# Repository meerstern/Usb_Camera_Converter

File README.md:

#  USBカメラ変換基板
#  Usb_Camera_Converter 
This board with PIC32MZ is a converter that captures from a UVC(Usb Video Class) standard Usb camera and converts it to a BMP or JPG image.

  * 10秒間隔インターバル記録した映像をコマ送り編集で動画化した例  
 
## 概要
  * 本変換基板はUVC規格のUsbカメラからキャプチャしてBMPもしくはJPG画像に変換する基板です  
  * シリアルUARTコマンドもしくは基板上のボタンを押すことで画像ファイルとして記録されます  
  * インターバル設定をすることで設定した秒数間隔(1秒~最長6か月程度)で自動的にインターバル記録できます  
  * 変換した画像はTFカード(microSD互換)もしくはXmodem、Ymodemでマイコン等に転送できます  
  * 時刻管理(RTC)を内蔵しており、自動的に日付のフォルダを生成し、日付日時のファイル名で保存されます  
  * 保存可能なファイル形式(BMP/JPG)および解像度は接続するUsbカメラによって異なります
  * PCを介したシリアルコンソール上でインターバル設定やファイル形式、解像度等の設定が可能です  
  * 高フレームレートを要求しない、簡易的な記録や監視に適しています  
  
## 仕様
  * 電源電圧5V、電流800mA(microUSBもしくはピンヘッダから供給)以上の電源  
  * 時刻管理用電池CR1220搭載  
  * PIC32MZ USB HighSpeed(480MHz) Host機能によるUVCホスト(USBタイプA)  
  * PCを介したシリアルコンソール上から変更できるパラメータ:  
  記録インターバル、ファイル形式、画像解像度、日付時刻、  
  代替インタフェース設定、データフレームインターバル  
  * microTFカード対応(microSD、microSDHC、microSDXC互換)、128GBまで動作確認済  
  * 3色状態表示LED(青:電源、緑:ストリーミング中、赤:ストリーミングエラー)  
  * シリアルコンソールボーレート9600bps、データサイズ8bit、パリティ無、ストップ1bitが既定値です  
  * シリアルコンソール用のUsbドライバ(PL2303GL)は[Windows版][2]、[Mac版][3]して使用してください  
  * Linux版のシリアルコンソール用のUsbドライバはKernel 2.4.31以降、標準で組み込まれています  
  * microTFカードを介したファームウェアアップデート対応  
  * 各設定パラメータ情報は時刻と一緒に保持されます  
  * 基板サイズ25mm x65mm、穴M3x4(間隔19mm x43mm)  

## シリアルコンソール
  * インタラクティブなシリアルコンソールから各種設定を変更することができます  
  * ボーレート9600bps、データサイズ8bit、パリティ無、ストップ1bitが既定値です  
  * 日時コマンド一覧は下記の通りです  
  
| コマンド名 | コマンド | 引数 | 例 | 
|:-----------|:------------|:------------|:------------|
| 時刻設定 | tim= | hhmmss | tim=220212(Enterキー) |
| 時刻確認 | tim? | なし | tim?(Enterキー) |
| 日時設定 |	day= | YYMMDD | day=220305(Enterキー) | 
| 日時確認 |	day? | なし | day?(Enterキー) | 	

  * カメラ機能コマンド一覧は下記の通りです  

| コマンド名 | コマンド | 引数 | 例 | 
|:-----------|:------------|:------------|:------------|
| 条件取得 | dsps | なし | dsps(Enterキー) |
| 条件設定 | idx= | インデックス番号 | idx=12(Enterキー) |
|　条件確認 | idx? | なし | idx?(Enterキー) | 
|　画像取得(TFカード) | trg! | なし | trg!(Enterキー) | 
|　画像取得(xmodem) | xmd! | なし | xmd!(Enterキー) | 
|　画像取得(ymodem) | ymd! | なし | ymd!(Enterキー) | 
| インターバル設定 | int= | 秒数 | int=5(Enterキー) | 	
| インターバル確認 | int? | なし | int?(Enterキー) | 	
| 代替インタフェース設定 | alt= | インデックス番号 | alt=2(Enterキー) | 	
| 代替インタフェース確認 | alt? | なし | alt?(Enterキー) | 	
| データフレームインターバル設定 | dfi= | インデックス番号 | dfi=2(Enterキー) | 	
| データフレームインターバル確認 | dfi? | なし | dfi?(Enterキー) | 
| Bmp形式白黒変換モード設定 | mon= | 0 or 1 | mon=1(Enterキー) | 	
| Bmp形式白黒変換モード確認 | mon? | なし | mon?(Enterキー) | 

  * インターバル記録しない場合はint=-1を設定します  
  * 代替インタフェース設定を自動にする場合はalt=0を設定します(既定値)  
  * 代替インタフェースは1回のデータ転送のサイズを決定します  
  * 1回のデータ転送サイズが小さすぎる場合は画像フレームのタイミングに間に合わない可能性があります  
  * 1回のデータ転送サイズが大きすぎる場合は処理しきれない場合があります  
  * カメラの機種によって設定可能な代替インタフェース数やサイズが異なります  
  * Bmp形式白黒変換モードはファームバージョンv1.1.0以降で対応しています  
  * Bmp形式白黒変換モードはデフォルトでは無効化されています  
  * Bmp形式白黒変換モードは電源再投入やリセット等で設定が無効化されます  
  
  <br>

  * データフレームインターバルを自動にする場合はdfi=0を設定します(既定値)  
  * データフレームインターバルはデータ転送の間隔、カメラのフレームレートを決定します  
  * データフレームインターバルが短かすぎる場合、処理が間に合わない可能性があります  
  * データフレームインターバルが長すぎる場合、トリガを掛けてから保存されるまで時間を要する場合があります  
  * カメラの機種によって対応するデータフレームインターバルの数や大きさが異なります  
  
  * システム機能のコマンド一覧は下記の通りです  
  
| コマンド名 | コマンド | 引数 | 例 | 
|:-----------|:------------|:------------|:------------|
| ボーレート設定 | brt= | ボーレート | brt=9600(Enterキー) |
| ボーレート確認 | brt? | なし | brt?(Enterキー) |
| ソフトリセット |	rst! | なし | rst!(Enterキー) | 
| 一時停止 |	pus! | なし | pus?(Enterキー) | 	  
| 再開 |	rsm! | なし | rsm?(Enterキー) |
| ファームアップデート |	fup! | なし | fup?(Enterキー) |
| ヘルプ確認 |	help | なし | help(Enterキー) |

## 使い方  
### a.単体で使用する場合  
  1. 本変換基板のmicroUSBをPC等に接続し、Teraterm等からシリアルコンソールにアクセスします    
  2. Usbカメラを変換基板のUsbコネクタに接続します
  3. 初期設定状態で動作開始します(初期設定ではエラーメッセージが出る場合があります)
  4. dspsコマンドで設定可能な条件を表示します  
  5. 設定したいファイル形式、解像度の条件をインデックス番号でidxコマンドを用いて設定します  
  6. rst!コマンドでソフトリセットさせて設定した内容を反映させます  
  7. microTFカードを挿入します
  8. ストリーミング中を示す緑ランプが点灯したことを確認します 点灯しない場合は5.で別の番号を設定します  
  9. trg!コマンドもしくはボタンを押すと画像が保存されます    
  
### b.連携して使用する場合    
  1. 事前にPC等からa.の設定したいファイル形式、解像度の条件を設定します
  2. 本変換基板の外部電源に5Vを供給し、TX、RXをマイコン等に接続します    
  3. Usbカメラを変換基板のUsbコネクタに接続します
  4. microTFカードを挿入します
  5. ストリーミング中を示す緑ランプが点灯したことを確認します  
  6. trg!コマンドもしくはtrgピンをGNDに接続することで画像が保存されます  
  7. xmd!コマンドを送信後、xmodem(チェックサム有効)で受信できます  
  8. ymd!コマンドを送信後、ymodemで受信できます   
  9. ユーザ側でコードを実装することでSPI等を介して外部機器と通信できます  
  
### c.日付/時刻設定する場合
  1. 本変換基板のmicroUSBをPC等に接続し、Teraterm等からシリアルコンソールにアクセスします   
  2. day=コマンドで日付を設定します 例 22年3月14日の場合はday=220314(Enter)と入力します  
  3. tim=コマンドで時刻を設定します 例 午後1時23分34秒の場合はtim=132334(Enter)と入力します  
  4. day?コマンド、tim?コマンドで設定された日付、日時を確認します  　
  
   * 日付、時刻が1桁の場合は0で桁を埋めてください 

### d.ファームウェアアップデートする場合
  1. アップデートしたいファームウェアをTFカードのディレクトリ直下にいれます  
  2. ファイル名をimage.binに変更します  
  3. 変換基板にTFカードを挿入し、電源を供給します  
  4. Teraterm等からシリアルコンソールからfup!コマンドを実行します  
  5. 自動的に再起動し、ファームウェアアップデートが開始されます  
  6. Update Successを確認するかシリアルコンソールに表示されるバージョンを確認してください  

## 注意点
  * マイコン上で処理する都合上、完全なUVC規格でありません  
  * カメラによって動作しないor不安定な場合があります  
  * 動作確認済のUsbカメラはTestedCamera.csvをご確認ください  
  * ハイビジョン対応等の高機能カメラよりも200万画素程度の単機能カメラの方が安定して動く傾向があります  
  * 動画を切り出して画像に変換するため、最高でも1FPSです 高フレームレートを要求する用途には適しません  
  * ボタンやコマンドから取得命令後、ストリーミングデータから切り出し処理の都合上、タイムラグがあります  
  * BMP形式の場合、メモリの制約によって最大解像度は320x240です  
  * JPG形式の場合、解像度によって動作、非動作の場合があります  
  * 動画ファイル形式の記録はできません  
  * 電源不安定や電流が足りない場合、動作確認済のカメラであっても正常に動作しない場合があります  
  * 電流が足りない場合、microUSBとJ5 5Vピンの両方から5V電源を供給することで動作する場合があります  
  * フォーマット、解像度のインデックス番号はカメラ機種によって番号や設定可能な条件数が異なります  
  * カメラによってはBMPをサポートしていないカメラがあります  
  * モードによって動作しない場合、下記の設定を変更することで動作する場合があります  
   -代替インタフェース設定(altコマンド)  
   -データフレームインターバル設定(dfiコマンド) 
  * 設定を変更することで必ず動作できる保証はありません   
  * Xmodem/Ymodemによる転送は9600bpsの場合、1枚の画像で数10分前後転送に要します  
  * 各設定はソフトリセット後もしくは電源再投入後に反映されます  
  * 時刻管理電池の消耗や交換した場合、各設定パラメータ、時刻はリセットされます  
  * ファームウェアアップデート時はボーレート9600bpsで固定です   

## ファームウェアビルド方法
  * MPLAB X v5.45/XC32 v2.50/Harmoney3以降を用いてビルドしてください  
  * ブートローダ用のAppファームをビルドする際はリンカファイルにp32MZ2048EFG100withBOOTLD.ldを選択します  
  * 生成されたAppファームの*.binファイルをimage.binに変更してSDカードから更新コマンドを用いて更新してください    
  * デバッグ等でブートローダ未使用でファームをビルドする際はリンカファイルにp32MZ2048EFG100.ldを選択します  
  * 再度、ブートローダを書き込む際にはUsbCamBoot_v.XX_XXXXXX.hexをIPE等から書き込んでください  
  
## 応用編
  * LCDファームに書き換えることでSPI対応LCD(160x128、ST7735S)でモニタすることが可能です  
  * LCDモニタはBMPの場合、160x120解像度のみ対応しています    
  * ENABLE_JPGDECODEを有効化することでTJPGD3ライブラリを用いてJPGからBMPにデコードして描画できます    
  　解像度幅160、320、640、1280のみ、一部のカメラは未対応  
  * コードを公開しています 改造することで他の機器とすることが可能です  
  * UART(XMODEM/YMODEM)に比べてSPIを介して高速に転送できます  

| LCDピン | 変換基板ピン |  
|:-----------|:------------|
| VCC,LED | J7 3.3V | 
| GND | J7 GND | 
| CS |	J7 CS | 
| SCK |	J7 SCK |   
| SDA |	J7 MOSI | 
| AO |	J3 PGED | 
| RST |	J3 PGEC | 

## 販売サイト
  * [スイッチサイエンス][4]

[2]: https://www.prolific.com.tw/UserFiles/files/PL23XX_Prolific_DriverInstaller_v408.zip
[3]: https://www.prolific.com.tw/UserFiles/files/PL2303HXD_G_Mac%20Driver_v2_1_0_20210311.zip
[4]: https://www.switch-science.com/products/8130

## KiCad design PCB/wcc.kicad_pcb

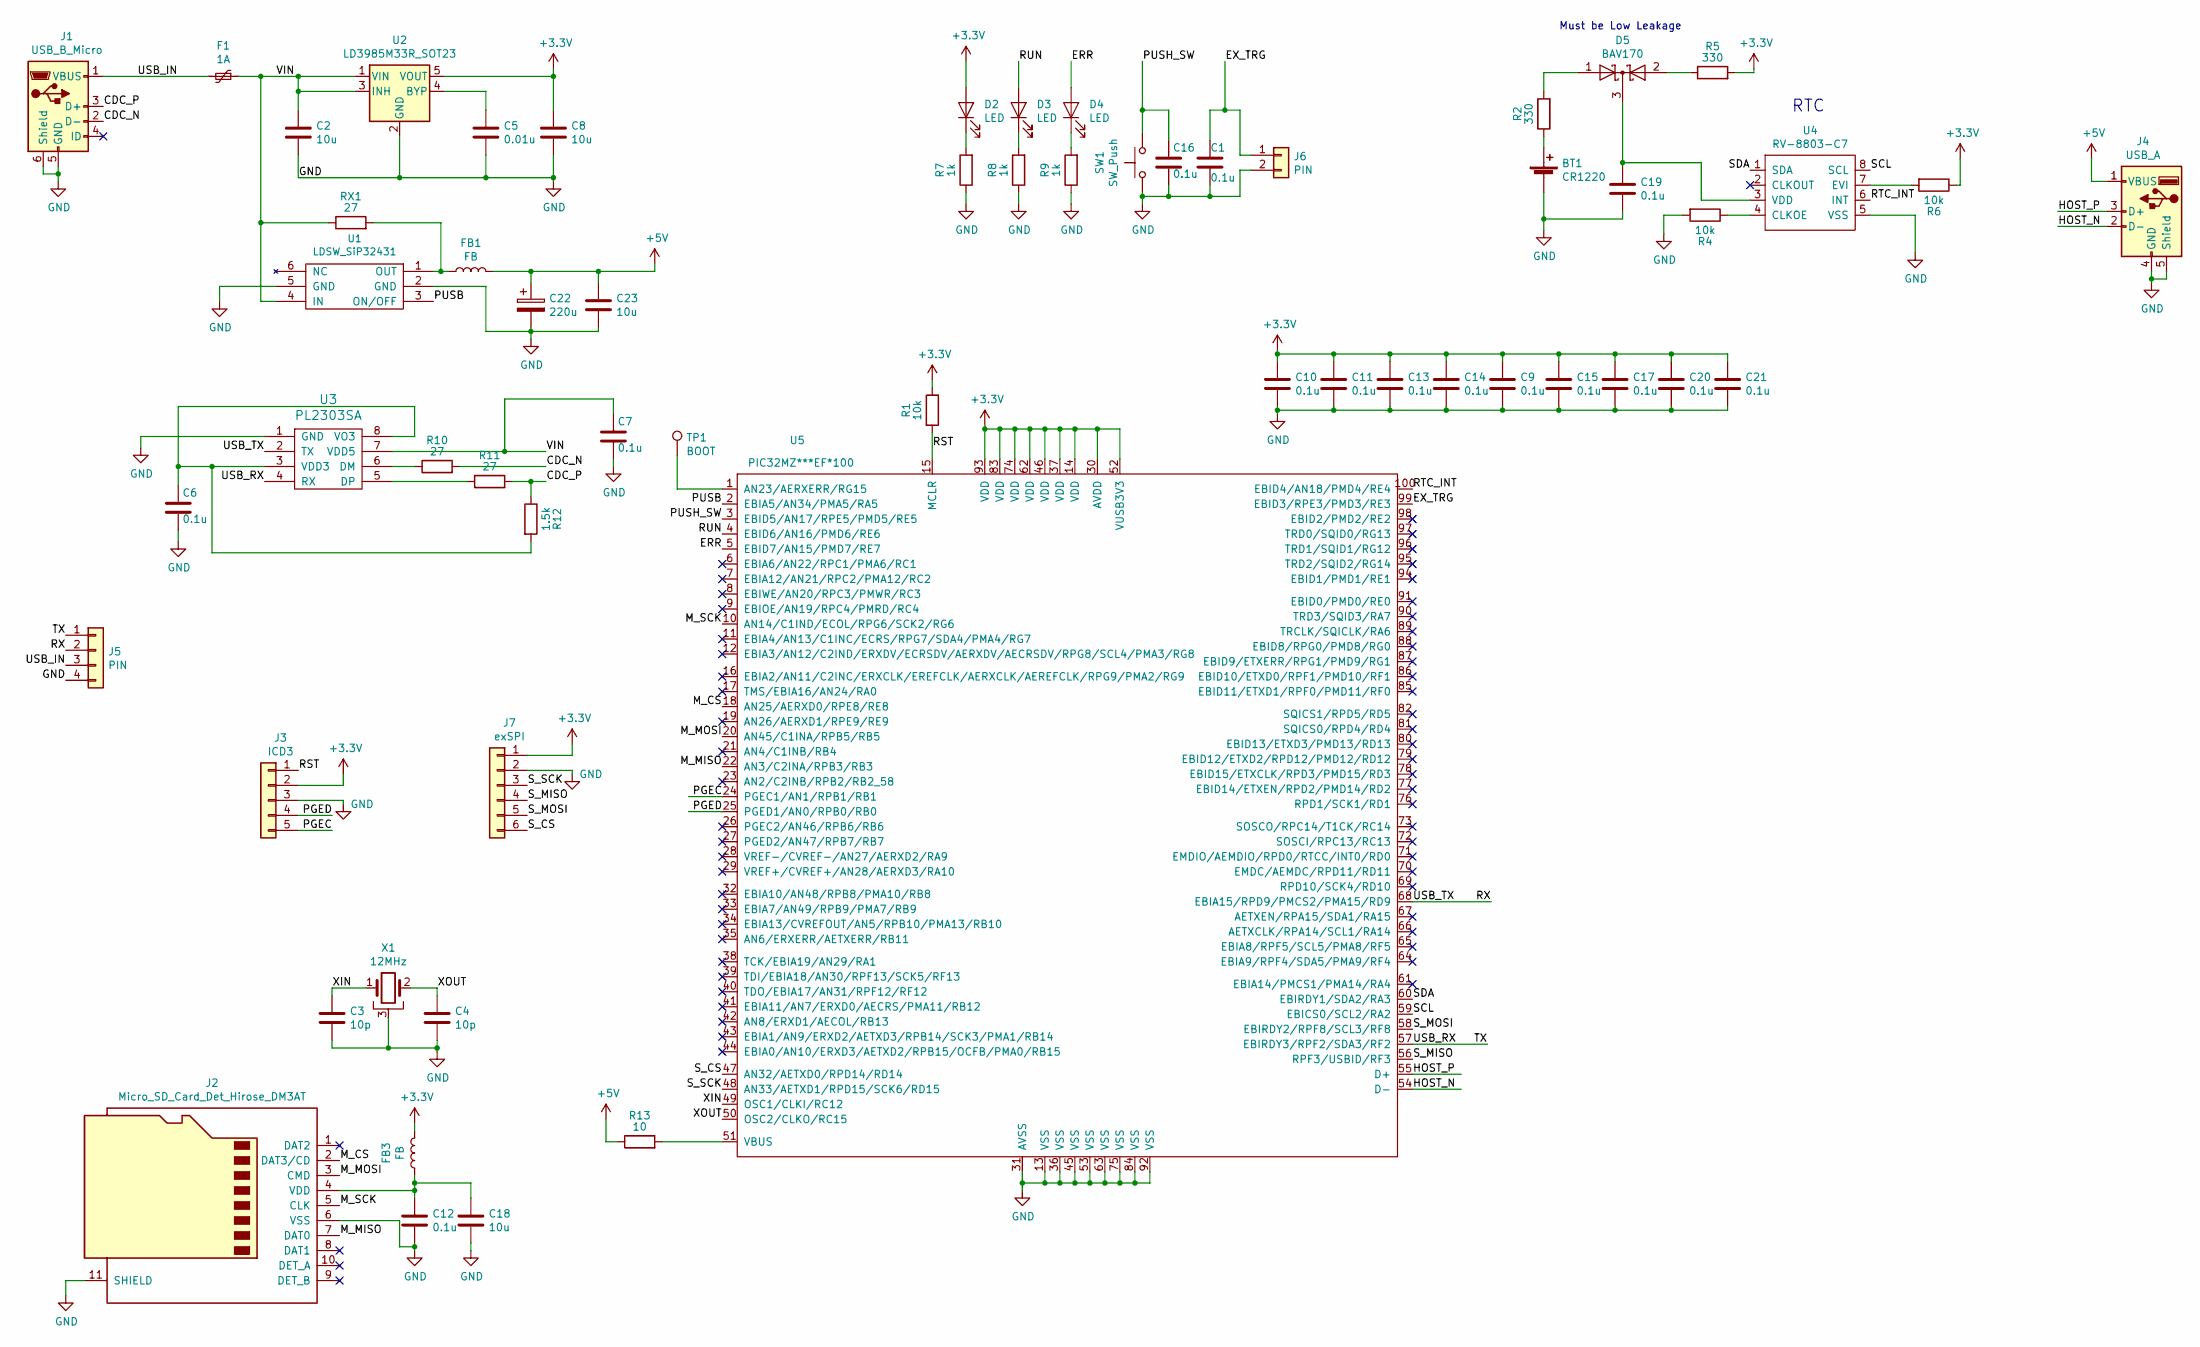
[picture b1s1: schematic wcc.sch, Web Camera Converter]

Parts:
BT1: CR1220; 2895
C1, C6, C7, C9, C10, C11, C12, C13, C14, C15, C16, C17, C19, C20, C21: 0.1u; C_0603_1608Metric
C2, C8, C18, C23: 10u; C_0805_2012Metric
C3, C4: 10p; C_0603_1608Metric
C5: 0.01u; C_0603_1608Metric
C22: 220u; CP_Elec_6.3x5.4_Nichicon
D2, D3, D4: LED; D_0603_1608Metric
D5: BAV170; SOT-23
F1: 1A; Fuse_1210_3225Metric
FB1, FB3: FB; L_0603_1608Metric
J1: USB_B_Micro; CONN-10118194-0001LF-FCI
J2: Micro_SD_Card_Det_Hirose_DM3AT; microSD_HC_Hirose_DM3AT-SF-PEJM5
J3: ICD3; PinHeader_1x05_P2.54mm_Vertical
J4: USB_A; USBHOST
J5: PIN; PinHeader_1x04_P2.54mm_Vertical
J6: PIN; PinHeader_1x02_P2.54mm_Vertical
J7: exSPI; PinHeader_1x06_P2.54mm_Vertical
R1, R4, R6: 10k; R_0603_1608Metric
R2, R5: 330; R_0603_1608Metric
R7, R8, R9: 1k; R_0603_1608Metric
R10, R11: 27; R_0603_1608Metric
R12: 1.5k; R_0603_1608Metric
R13: 10; R_0603_1608Metric
RX1: 27; R_0603_1608Metric
SW1: SW_Push; SKRPACE010
TP1: BOOT; TestPoint_Pad_D1.0mm
U1: LDSW_SiP32431; SOT-363_SC-70-6
U2: LD3985M33R_SOT23; SOT-23-5
U3: PL2303SA; SOIC-8_3.9x4.9mm_P1.27mm
U4: RV-8803-C7
U5: PIC32MZ***EF*100; TQFP-100_12x12mm_P0.4mm
X1: 12MHz; FA238V

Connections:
+3V3: C8.1, C9.1, C10.1, C11.1, C13.1, C14.1, C15.1, C17.1, C20.1, C21.1, D2.2 (A), FB3.2, J3.2, J7.1, R1.2, R5.2, R6.1, U2.5 (VOUT), U5.14 (VDD), U5.30 (AVDD), U5.37 (VDD), U5.46 (VDD), U5.52 (VUSB3V3), U5.62 (VDD), U5.74 (VDD), U5.83 (VDD), U5.93 (VDD)
+5V: C22.1, C23.1, FB1.2, J4.1 (VBUS), R13.1
/CDC_N: J1.2 (D-), R10.2
/CDC_P: J1.3 (D+), R11.2, R12.1
/ERR: D4.2 (A), U5.5 (EBID7/AN15/PMD7/RE7)
/EX_TRG: C1.1, J6.1, U5.99 (EBID3/RPE3/PMD3/RE3)
/HOST_N: J4.2 (D-), U5.54 (D-)
/HOST_P: J4.3 (D+), U5.55 (D+)
/M_CS: J2.2 (DAT3/CD), U5.18 (AN25/AERXD0/RPE8/RE8)
/M_MISO: J2.7 (DAT0), U5.22 (AN3/C2INA/RPB3/RB3)
/M_MOSI: J2.3 (CMD), U5.20 (AN45/C1INA/RPB5/RB5)
/M_SCK: J2.5 (CLK), U5.10 (AN14/C1IND/ECOL/RPG6/SCK2/RG6)
/PGEC: J3.5, U5.24 (PGEC1/AN1/RPB1/RB1)
/PGED: J3.4, U5.25 (PGED1/AN0/RPB0/RB0)
/PUSB: U1.3 (ON/OFF), U5.2 (EBIA5/AN34/PMA5/RA5)
/PUSH_SW: C16.1, SW1.2, U5.3 (EBID5/AN17/RPE5/PMD5/RE5)
/RST: J3.1, R1.1, U5.15 (MCLR)
/RTC_INT: U4.6 (INT), U5.100 (EBID4/AN18/PMD4/RE4)
/RUN: D3.2 (A), U5.4 (EBID6/AN16/PMD6/RE6)
/RX: J5.2, U3.2 (TX), U5.68 (EBIA15/RPD9/PMCS2/PMA15/RD9)
/SCL: U4.8 (SCL), U5.59 (EBICS0/SCL2/RA2)
/SDA: U4.1 (SDA), U5.60 (EBIRDY1/SDA2/RA3)
/S_CS: J7.6, U5.47 (AN32/AETXD0/RPD14/RD14)
/S_MISO: J7.4, U5.56 (RPF3/USBID/RF3)
/S_MOSI: J7.5, U5.58 (EBIRDY2/RPF8/SCL3/RF8)
/S_SCK: J7.3, U5.48 (AN33/AETXD1/RPD15/SCK6/RD15)
/TX: J5.1, U3.4 (RX), U5.57 (EBIRDY3/RPF2/SDA3/RF2)
/USB_IN: F1.2, J1.1 (VBUS), J5.3
/VIN: C2.1, C7.1, F1.1, RX1.1, U1.4 (IN), U2.1 (VIN), U2.3 (INH), U3.7 (VDD5)
/XIN: C3.1, U5.49 (OSC1/CLKI/RC12), X1.1
/XOUT: C4.1, U5.50 (OSC2/CLKO/RC15), X1.2
GND: BT1.2 (-), C1.2, C2.2, C3.2, C4.2, C5.2, C6.2, C7.2, C8.2, C9.2, C10.2, C11.2, C12.2, C13.2, C14.2, C15.2, C16.2, C17.2, C18.2, C19.2, C20.2, C21.2, C22.2, C23.2, J1.5 (GND), J1.6 (Shield), J2.6 (VSS), J2.11 (SHIELD), J3.3, J4.4 (GND), J4.5 (Shield), J5.4, J6.2, J7.2, R4.2, R7.1, R8.1, R9.1, SW1.1, U1.2 (GND), U1.5 (GND), U2.2 (GND), U3.1 (GND), U4.5 (VSS), U5.13 (VSS), U5.31 (AVSS), U5.36 (VSS), U5.45 (VSS), U5.53 (VSS), U5.63 (VSS), U5.75 (VSS), U5.84 (VSS), U5.92 (VSS), X1.3
unnamed: BT1.1 (+), R2.1
unnamed: C5.1, U2.4 (BYP)
unnamed: C6.1, R12.2, U3.3 (VDD3), U3.8 (VO3)
unnamed: C12.1, C18.1, FB3.1, J2.4 (VDD)
unnamed: C19.1, D5.3 (K), U4.3 (VDD)
unnamed: D2.1 (K), R7.2
unnamed: D3.1 (K), R8.2
unnamed: D4.1 (K), R9.2
unnamed: D5.1 (A), R2.2
unnamed: D5.2 (A), R5.1
unnamed: FB1.1, RX1.2, U1.1 (OUT)
unnamed: R4.1, U4.4 (CLKOE)
unnamed: R6.2, U4.7 (EVI)
unnamed: R10.1, U3.6 (DM)
unnamed: R11.1, U3.5 (DP)
unnamed: R13.2, U5.51 (VBUS)
unnamed: TP1.1, U5.1 (AN23/AERXERR/RG15)

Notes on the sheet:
RTC
Must be Low Leakage

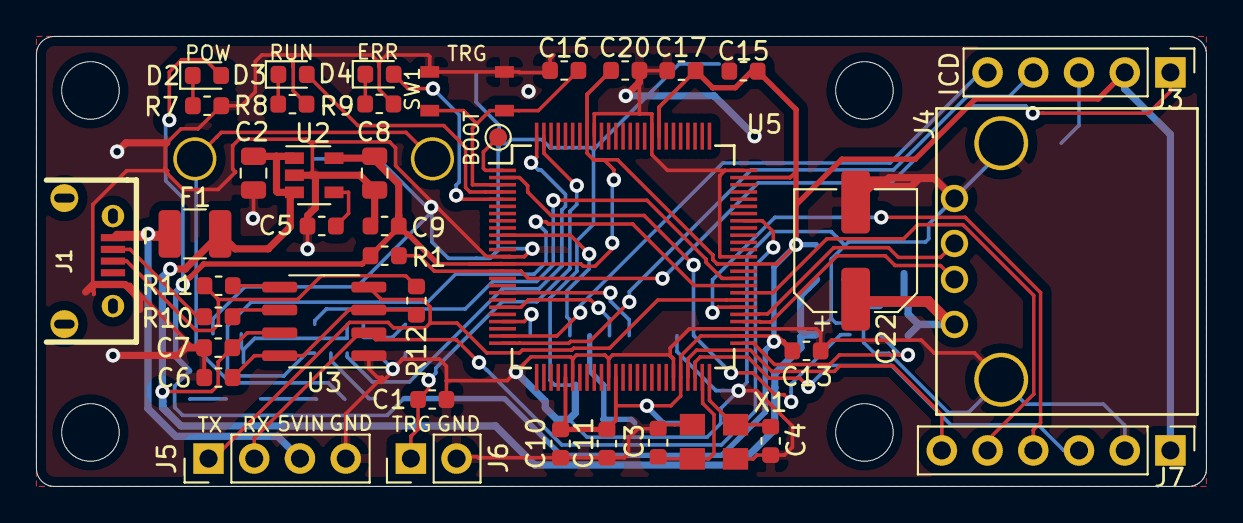
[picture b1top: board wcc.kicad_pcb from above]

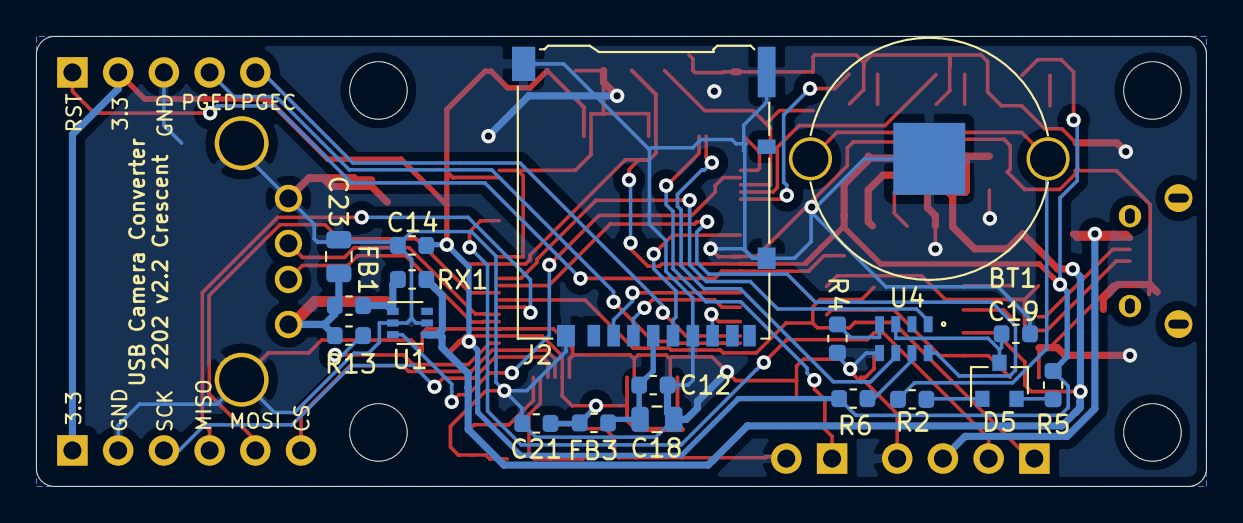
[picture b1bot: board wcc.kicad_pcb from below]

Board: 2 copper layers, 65.0 x 25.0 mm, 63 parts (19 on the bottom side), 49 nets.

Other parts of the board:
REF1, REF2, REF3, REF4: MountingHole_3.2mm_M3

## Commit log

2022-03-23 Add PCB Files
2022-04-17 Add images
2022-04-17 add image
2022-04-17 Add Tested Camera list
2022-04-19 Add firm
2022-04-20 add じふぃまっげ
2022-04-20 Revert "add じふぃまっげ"
    This reverts commit 6ead67896466d1b7939286707e8fd9013db0f11c.
2022-10-04 Add Monochrome Mode for Bitmap
2022-10-05 update link
